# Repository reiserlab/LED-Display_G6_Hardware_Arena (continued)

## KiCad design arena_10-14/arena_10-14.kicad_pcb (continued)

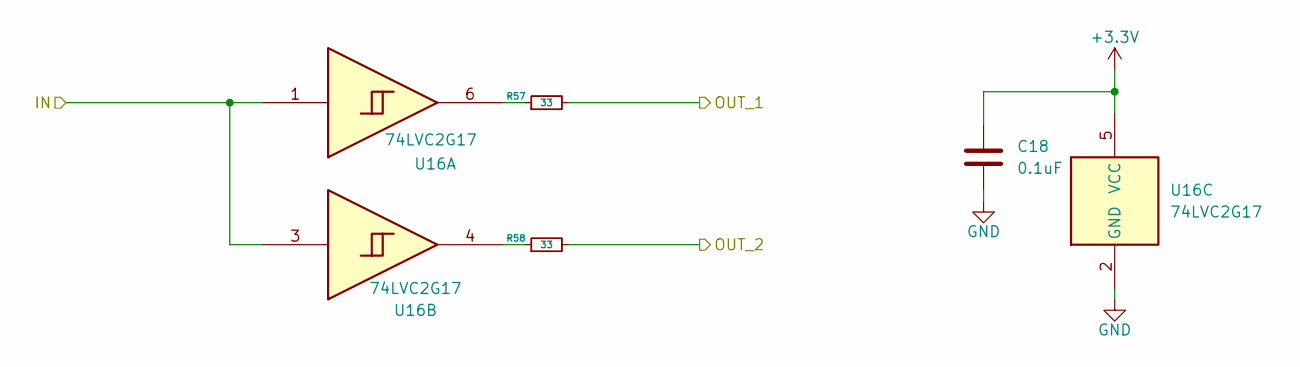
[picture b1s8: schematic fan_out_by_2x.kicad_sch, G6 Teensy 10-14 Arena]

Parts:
C18: 0.1uF; C_0402_1005Metric; LCSC Part # C1525
R57, R58: 33; R_0402_1005Metric; LCSC Part # C25105
U16: 74LVC2G17; SOT-23-6; LCSC Part # C7394037

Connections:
+3.3V: C18.1, U16.5 (VCC); also elsewhere on the board
/Fan Out/PAN.CS_00_P1: R58.2; also elsewhere on the board
/Fan Out/PAN.CS_00_P6: R57.2; also elsewhere on the board
/Fan Out/TNY.CS_00: U16.1, U16.3; also elsewhere on the board
GND: C18.2, U16.2 (GND); also elsewhere on the board
unnamed: R57.1, U16.6
unnamed: R58.1, U16.4

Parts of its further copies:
C19, C20, C21, C22, C23, C24, C25, C26, C27, C28, C29, C30, C31, C32, C33, C34, C35, C36, C37: 0.1uF; C_0402_1005Metric; LCSC Part # C1525
R59, R60, R61, R62, R63, R64, R65, R66, R67, R68, R69, R70, R71, R72, R73, R74, R75, R76, R77, R78, R79, R80, R81, R82, R83, R84, R85, R86, R87, R88, R89, R90, R91, R92, R93, R94, R95, R96: 33; R_0402_1005Metric; LCSC Part # C25105
U17, U18, U19, U20, U21, U22, U23, U24, U25, U26, U27, U28, U29, U30, U31, U32, U33, U34, U35: 74LVC2G17; SOT-23-6; LCSC Part # C7394037

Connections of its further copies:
+3.3V: C19.1, C20.1, C21.1, C22.1, C23.1, C24.1, C25.1, C26.1, C27.1, C28.1, C29.1, C30.1, C31.1, C32.1, C33.1, C34.1, C35.1, C36.1, C37.1, U17.5 (VCC), U18.5 (VCC), U19.5 (VCC), U20.5 (VCC), U21.5 (VCC), U22.5 (VCC), U23.5 (VCC), U24.5 (VCC), U25.5 (VCC), U26.5 (VCC), U27.5 (VCC), U28.5 (VCC), U29.5 (VCC), U30.5 (VCC), U31.5 (VCC), U32.5 (VCC), U33.5 (VCC), U34.5 (VCC), U35.5 (VCC); also elsewhere on the board
/Fan Out/PAN.CS_01_P1: R60.2; also elsewhere on the board
/Fan Out/PAN.CS_01_P6: R59.2; also elsewhere on the board
/Fan Out/PAN.CS_02_P1: R62.2; also elsewhere on the board
/Fan Out/PAN.CS_02_P6: R61.2; also elsewhere on the board
/Fan Out/PAN.CS_03_P1: R64.2; also elsewhere on the board
/Fan Out/PAN.CS_03_P6: R63.2; also elsewhere on the board
/Fan Out/PAN.CS_04_P2: R66.2; also elsewhere on the board
/Fan Out/PAN.CS_04_P7: R65.2; also elsewhere on the board
/Fan Out/PAN.CS_05_P2: R68.2; also elsewhere on the board
/Fan Out/PAN.CS_05_P7: R67.2; also elsewhere on the board
/Fan Out/PAN.CS_06_P2: R70.2; also elsewhere on the board
/Fan Out/PAN.CS_06_P7: R69.2; also elsewhere on the board
/Fan Out/PAN.CS_07_P2: R72.2; also elsewhere on the board
/Fan Out/PAN.CS_07_P7: R71.2; also elsewhere on the board
/Fan Out/PAN.CS_08_P3: R74.2; also elsewhere on the board
/Fan Out/PAN.CS_08_P8: R73.2; also elsewhere on the board
/Fan Out/PAN.CS_09_P3: R76.2; also elsewhere on the board
/Fan Out/PAN.CS_09_P8: R75.2; also elsewhere on the board
/Fan Out/PAN.CS_10_P3: R78.2; also elsewhere on the board
/Fan Out/PAN.CS_10_P8: R77.2; also elsewhere on the board
/Fan Out/PAN.CS_11_P3: R80.2; also elsewhere on the board
/Fan Out/PAN.CS_11_P8: R79.2; also elsewhere on the board
/Fan Out/PAN.CS_12_P4: R82.2; also elsewhere on the board
/Fan Out/PAN.CS_12_P9: R81.2; also elsewhere on the board
/Fan Out/PAN.CS_13_P4: R84.2; also elsewhere on the board
/Fan Out/PAN.CS_13_P9: R83.2; also elsewhere on the board
/Fan Out/PAN.CS_14_P4: R86.2; also elsewhere on the board
/Fan Out/PAN.CS_14_P9: R85.2; also elsewhere on the board
/Fan Out/PAN.CS_15_P4: R88.2; also elsewhere on the board
/Fan Out/PAN.CS_15_P9: R87.2; also elsewhere on the board
/Fan Out/PAN.CS_16_P5: R90.2; also elsewhere on the board
/Fan Out/PAN.CS_16_P10: R89.2; also elsewhere on the board
/Fan Out/PAN.CS_17_P5: R92.2; also elsewhere on the board
/Fan Out/PAN.CS_17_P10: R91.2; also elsewhere on the board
/Fan Out/PAN.CS_18_P5: R94.2; also elsewhere on the board
/Fan Out/PAN.CS_18_P10: R93.2; also elsewhere on the board
/Fan Out/PAN.CS_19_P5: R96.2; also elsewhere on the board
/Fan Out/PAN.CS_19_P10: R95.2; also elsewhere on the board
/Fan Out/TNY.CS_01: U17.1, U17.3; also elsewhere on the board
/Fan Out/TNY.CS_02: U18.1, U18.3; also elsewhere on the board
/Fan Out/TNY.CS_03: U19.1, U19.3; also elsewhere on the board
/Fan Out/TNY.CS_04: U20.1, U20.3; also elsewhere on the board
/Fan Out/TNY.CS_05: U21.1, U21.3; also elsewhere on the board
/Fan Out/TNY.CS_06: U22.1, U22.3; also elsewhere on the board
/Fan Out/TNY.CS_07: U23.1, U23.3; also elsewhere on the board
/Fan Out/TNY.CS_08: U24.1, U24.3; also elsewhere on the board
/Fan Out/TNY.CS_09: U25.1, U25.3; also elsewhere on the board
/Fan Out/TNY.CS_10: U26.1, U26.3; also elsewhere on the board
/Fan Out/TNY.CS_11: U27.1, U27.3; also elsewhere on the board
/Fan Out/TNY.CS_12: U28.1, U28.3; also elsewhere on the board
/Fan Out/TNY.CS_13: U29.1, U29.3; also elsewhere on the board
/Fan Out/TNY.CS_14: U30.1, U30.3; also elsewhere on the board
/Fan Out/TNY.CS_15: U31.1, U31.3; also elsewhere on the board
/Fan Out/TNY.CS_16: U32.1, U32.3; also elsewhere on the board
/Fan Out/TNY.CS_17: U33.1, U33.3; also elsewhere on the board
/Fan Out/TNY.CS_18: U34.1, U34.3; also elsewhere on the board
/Fan Out/TNY.CS_19: U35.1, U35.3; also elsewhere on the board
GND: C19.2, C20.2, C21.2, C22.2, C23.2, C24.2, C25.2, C26.2, C27.2, C28.2, C29.2, C30.2, C31.2, C32.2, C33.2, C34.2, C35.2, C36.2, C37.2, U17.2 (GND), U18.2 (GND), U19.2 (GND), U20.2 (GND), U21.2 (GND), U22.2 (GND), U23.2 (GND), U24.2 (GND), U25.2 (GND), U26.2 (GND), U27.2 (GND), U28.2 (GND), U29.2 (GND), U30.2 (GND), U31.2 (GND), U32.2 (GND), U33.2 (GND), U34.2 (GND), U35.2 (GND); also elsewhere on the board
unnamed: R59.1, U17.6
unnamed: R60.1, U17.4
unnamed: R61.1, U18.6
unnamed: R62.1, U18.4
unnamed: R63.1, U19.6
unnamed: R64.1, U19.4
unnamed: R65.1, U20.6
unnamed: R66.1, U20.4
unnamed: R67.1, U21.6
unnamed: R68.1, U21.4
unnamed: R69.1, U22.6
unnamed: R70.1, U22.4
unnamed: R71.1, U23.6
unnamed: R72.1, U23.4
unnamed: R73.1, U24.6
unnamed: R74.1, U24.4
unnamed: R75.1, U25.6
unnamed: R76.1, U25.4
unnamed: R77.1, U26.6
unnamed: R78.1, U26.4
unnamed: R79.1, U27.6
unnamed: R80.1, U27.4
unnamed: R81.1, U28.6
unnamed: R82.1, U28.4
unnamed: R83.1, U29.6
unnamed: R84.1, U29.4
unnamed: R85.1, U30.6
unnamed: R86.1, U30.4
unnamed: R87.1, U31.6
unnamed: R88.1, U31.4
unnamed: R89.1, U32.6
unnamed: R90.1, U32.4
unnamed: R91.1, U33.6
unnamed: R92.1, U33.4
unnamed: R93.1, U34.6
unnamed: R94.1, U34.4
unnamed: R95.1, U35.6
unnamed: R96.1, U35.4

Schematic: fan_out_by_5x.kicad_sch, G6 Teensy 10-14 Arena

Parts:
C6, C7, C8: 0.1uF; C_0402_1005Metric; LCSC Part # C1525
R33, R34, R35, R36, R37, R38: 33; R_0402_1005Metric; LCSC Part # C25105
U4, U5, U6: 74LVC2G17; SOT-23-6; LCSC Part # C7394037

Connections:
+3.3V: C6.1, C7.1, C8.1, U4.5 (VCC), U5.5 (VCC), U6.5 (VCC); also elsewhere on the board
/Fan Out/PAN.SCK_B0_P1: R33.2; also elsewhere on the board
/Fan Out/PAN.SCK_B0_P2: R34.2; also elsewhere on the board
/Fan Out/PAN.SCK_B0_P3: R35.2; also elsewhere on the board
/Fan Out/PAN.SCK_B0_P4: R36.2; also elsewhere on the board
/Fan Out/PAN.SCK_B0_P5: R37.2; also elsewhere on the board
/Fan Out/SCK B0 fan out to P1-P6/OUT_6: R38.2
/Fan Out/TNY.SCK_B0: U4.1, U4.3, U5.1, U5.3, U6.1, U6.3; also elsewhere on the board
GND: C6.2, C7.2, C8.2, U4.2 (GND), U5.2 (GND), U6.2 (GND); also elsewhere on the board
unnamed: R33.1, U4.6
unnamed: R34.1, U4.4
unnamed: R35.1, U5.6
unnamed: R36.1, U5.4
unnamed: R37.1, U6.6
unnamed: R38.1, U6.4

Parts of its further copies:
C9, C10, C11, C12, C13, C14, C15, C16, C17, C38, C39, C40, C41, C42, C43: 0.1uF; C_0402_1005Metric; LCSC Part # C1525
R39, R40, R41, R42, R43, R44, R45, R46, R47, R48, R49, R50, R51, R52, R53, R54, R55, R56, R97, R98, R99, R100, R101, R102, R103, R104, R105, R106, R107, R108: 33; R_0402_1005Metric; LCSC Part # C25105
U7, U8, U9, U10, U11, U12, U13, U14, U15, U36, U37, U38, U39, U40, U41: 74LVC2G17; SOT-23-6; LCSC Part # C7394037

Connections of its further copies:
+3.3V: C9.1, C10.1, C11.1, C12.1, C13.1, C14.1, C15.1, C16.1, C17.1, C38.1, C39.1, C40.1, C41.1, C42.1, C43.1, U7.5 (VCC), U8.5 (VCC), U9.5 (VCC), U10.5 (VCC), U11.5 (VCC), U12.5 (VCC), U13.5 (VCC), U14.5 (VCC), U15.5 (VCC), U36.5 (VCC), U37.5 (VCC), U38.5 (VCC), U39.5 (VCC), U40.5 (VCC), U41.5 (VCC); also elsewhere on the board
/Fan Out/COPI B0 fan out to P1-P6/OUT_6: R44.2
/Fan Out/COPI B1 fan out to P6-P10/OUT_6: R56.2
/Fan Out/EINT fan out to P1-P5/OUT_6: R108.2
/Fan Out/EINT fan out to P6-P10/OUT_6: R102.2
/Fan Out/PAN.COPI_B0_P1: R39.2; also elsewhere on the board
/Fan Out/PAN.COPI_B0_P2: R40.2; also elsewhere on the board
/Fan Out/PAN.COPI_B0_P3: R41.2; also elsewhere on the board
/Fan Out/PAN.COPI_B0_P4: R42.2; also elsewhere on the board
/Fan Out/PAN.COPI_B0_P5: R43.2; also elsewhere on the board
/Fan Out/PAN.COPI_B1_P6: R51.2; also elsewhere on the board
/Fan Out/PAN.COPI_B1_P7: R52.2; also elsewhere on the board
/Fan Out/PAN.COPI_B1_P8: R53.2; also elsewhere on the board
/Fan Out/PAN.COPI_B1_P9: R54.2; also elsewhere on the board
/Fan Out/PAN.COPI_B1_P10: R55.2; also elsewhere on the board
/Fan Out/PAN.EINT_P1: R103.2; also elsewhere on the board
/Fan Out/PAN.EINT_P2: R104.2; also elsewhere on the board
/Fan Out/PAN.EINT_P3: R105.2; also elsewhere on the board
/Fan Out/PAN.EINT_P4: R106.2; also elsewhere on the board
/Fan Out/PAN.EINT_P5: R107.2; also elsewhere on the board
/Fan Out/PAN.EINT_P6: R97.2; also elsewhere on the board
/Fan Out/PAN.EINT_P7: R98.2; also elsewhere on the board
/Fan Out/PAN.EINT_P8: R99.2; also elsewhere on the board
/Fan Out/PAN.EINT_P9: R100.2; also elsewhere on the board
/Fan Out/PAN.EINT_P10: R101.2; also elsewhere on the board
/Fan Out/PAN.SCK_B1_P6: R45.2; also elsewhere on the board
/Fan Out/PAN.SCK_B1_P7: R46.2; also elsewhere on the board
/Fan Out/PAN.SCK_B1_P8: R47.2; also elsewhere on the board
/Fan Out/PAN.SCK_B1_P9: R48.2; also elsewhere on the board
/Fan Out/PAN.SCK_B1_P10: R49.2; also elsewhere on the board
/Fan Out/SCK B1 fan out to P6-P10/OUT_6: R50.2
/Fan Out/TNY.COPI_B0: U7.1, U7.3, U8.1, U8.3, U9.1, U9.3; also elsewhere on the board
/Fan Out/TNY.COPI_B1: U13.1, U13.3, U14.1, U14.3, U15.1, U15.3; also elsewhere on the board
/Fan Out/TNY.EINT: U36.1, U36.3, U37.1, U37.3, U38.1, U38.3, U39.1, U39.3, U40.1, U40.3, U41.1, U41.3; also elsewhere on the board
/Fan Out/TNY.SCK_B1: U10.1, U10.3, U11.1, U11.3, U12.1, U12.3; also elsewhere on the board
GND: C9.2, C10.2, C11.2, C12.2, C13.2, C14.2, C15.2, C16.2, C17.2, C38.2, C39.2, C40.2, C41.2, C42.2, C43.2, U7.2 (GND), U8.2 (GND), U9.2 (GND), U10.2 (GND), U11.2 (GND), U12.2 (GND), U13.2 (GND), U14.2 (GND), U15.2 (GND), U36.2 (GND), U37.2 (GND), U38.2 (GND), U39.2 (GND), U40.2 (GND), U41.2 (GND); also elsewhere on the board
unnamed: R39.1, U7.6
unnamed: R40.1, U7.4
unnamed: R41.1, U8.6
unnamed: R42.1, U8.4
unnamed: R43.1, U9.6
unnamed: R44.1, U9.4
unnamed: R45.1, U10.6
unnamed: R46.1, U10.4
unnamed: R47.1, U11.6
unnamed: R48.1, U11.4
unnamed: R49.1, U12.6
unnamed: R50.1, U12.4
unnamed: R51.1, U13.6
unnamed: R52.1, U13.4
unnamed: R53.1, U14.6
unnamed: R54.1, U14.4
unnamed: R55.1, U15.6
unnamed: R56.1, U15.4
unnamed: R97.1, U36.6
unnamed: R98.1, U36.4
unnamed: R99.1, U37.6
unnamed: R100.1, U37.4
unnamed: R101.1, U38.6
unnamed: R102.1, U38.4
unnamed: R103.1, U39.6
unnamed: R104.1, U39.4
unnamed: R105.1, U40.6
unnamed: R106.1, U40.4
unnamed: R107.1, U41.6
unnamed: R108.1, U41.4

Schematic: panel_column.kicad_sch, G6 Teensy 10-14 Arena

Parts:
C48: 100uF; C_1210_3225Metric; LCSC Part # C7432790
F1: 1.1A PTC; Fuse_1206_3216Metric; LCSC Part # C126818
J7, J8: Conn_01x05; PinSocket_1x05_P2.54mm_Vertical; LCSC Part # C50950
P1: NA; Panel_Silk; not fitted

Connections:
+5V: F1.1; also elsewhere on the board
/Panels/Panel Column P1/Column Buffer/CIPO_IN: J7.5; also elsewhere on the board
/Panels/Panel Column P1/Column Buffer/COPI_OUT: J7.4; also elsewhere on the board
/Panels/Panel Column P1/Column Buffer/CS0_OUT: J8.1; also elsewhere on the board
/Panels/Panel Column P1/Column Buffer/CS1_OUT: J8.2; also elsewhere on the board
/Panels/Panel Column P1/Column Buffer/CS2_OUT: J8.3; also elsewhere on the board
/Panels/Panel Column P1/Column Buffer/CS_3OUT: J8.4; also elsewhere on the board
/Panels/Panel Column P1/Column Buffer/EINT_OUT: J8.5; also elsewhere on the board
/Panels/Panel Column P1/Column Buffer/SCK_OUT: J7.3; also elsewhere on the board
GND: C48.1, J7.2; also elsewhere on the board
unnamed: C48.2, F1.2, J7.1

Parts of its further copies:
C49, C54, C59, C64, C69, C74, C79, C84, C152: 100uF; C_1210_3225Metric; LCSC Part # C7432790
F2, F3, F4, F5, F6, F7, F8, F9, F10: 1.1A PTC; Fuse_1206_3216Metric; LCSC Part # C126818
J9, J10, J11, J12, J13, J14, J15, J16, J17, J18, J19, J20, J21, J22, J23, J24, J32, J33: Conn_01x05; PinSocket_1x05_P2.54mm_Vertical; LCSC Part # C50950
P2, P3, P4, P5, P6, P7, P8, P9, P10: NA; Panel_Silk; not fitted

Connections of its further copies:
+5V: F2.1, F3.1, F4.1, F5.1, F6.1, F7.1, F8.1, F9.1, F10.1; also elsewhere on the board
/Panels/Panel Column P2/Column Buffer/CIPO_IN: J9.5; also elsewhere on the board
/Panels/Panel Column P2/Column Buffer/COPI_OUT: J9.4; also elsewhere on the board
/Panels/Panel Column P2/Column Buffer/CS0_OUT: J10.1; also elsewhere on the board
/Panels/Panel Column P2/Column Buffer/CS1_OUT: J10.2; also elsewhere on the board
/Panels/Panel Column P2/Column Buffer/CS2_OUT: J10.3; also elsewhere on the board
/Panels/Panel Column P2/Column Buffer/CS_3OUT: J10.4; also elsewhere on the board
/Panels/Panel Column P2/Column Buffer/EINT_OUT: J10.5; also elsewhere on the board
/Panels/Panel Column P2/Column Buffer/SCK_OUT: J9.3; also elsewhere on the board
/Panels/Panel Column P3/Column Buffer/CIPO_IN: J11.5; also elsewhere on the board
/Panels/Panel Column P3/Column Buffer/COPI_OUT: J11.4; also elsewhere on the board
/Panels/Panel Column P3/Column Buffer/CS0_OUT: J12.1; also elsewhere on the board
/Panels/Panel Column P3/Column Buffer/CS1_OUT: J12.2; also elsewhere on the board
/Panels/Panel Column P3/Column Buffer/CS2_OUT: J12.3; also elsewhere on the board
/Panels/Panel Column P3/Column Buffer/CS_3OUT: J12.4; also elsewhere on the board
/Panels/Panel Column P3/Column Buffer/EINT_OUT: J12.5; also elsewhere on the board
/Panels/Panel Column P3/Column Buffer/SCK_OUT: J11.3; also elsewhere on the board
/Panels/Panel Column P4/Column Buffer/CIPO_IN: J13.5; also elsewhere on the board
/Panels/Panel Column P4/Column Buffer/COPI_OUT: J13.4; also elsewhere on the board
/Panels/Panel Column P4/Column Buffer/CS0_OUT: J14.1; also elsewhere on the board
/Panels/Panel Column P4/Column Buffer/CS1_OUT: J14.2; also elsewhere on the board
/Panels/Panel Column P4/Column Buffer/CS2_OUT: J14.3; also elsewhere on the board
/Panels/Panel Column P4/Column Buffer/CS_3OUT: J14.4; also elsewhere on the board
/Panels/Panel Column P4/Column Buffer/EINT_OUT: J14.5; also elsewhere on the board
/Panels/Panel Column P4/Column Buffer/SCK_OUT: J13.3; also elsewhere on the board
/Panels/Panel Column P5/Column Buffer/CIPO_IN: J15.5; also elsewhere on the board
/Panels/Panel Column P5/Column Buffer/COPI_OUT: J15.4; also elsewhere on the board
/Panels/Panel Column P5/Column Buffer/CS0_OUT: J16.1; also elsewhere on the board
/Panels/Panel Column P5/Column Buffer/CS1_OUT: J16.2; also elsewhere on the board
/Panels/Panel Column P5/Column Buffer/CS2_OUT: J16.3; also elsewhere on the board
/Panels/Panel Column P5/Column Buffer/CS_3OUT: J16.4; also elsewhere on the board
/Panels/Panel Column P5/Column Buffer/EINT_OUT: J16.5; also elsewhere on the board
/Panels/Panel Column P5/Column Buffer/SCK_OUT: J15.3; also elsewhere on the board
/Panels/Panel Column P6/Column Buffer/CIPO_IN: J32.5; also elsewhere on the board
/Panels/Panel Column P6/Column Buffer/COPI_OUT: J32.4; also elsewhere on the board
/Panels/Panel Column P6/Column Buffer/CS0_OUT: J33.1; also elsewhere on the board
/Panels/Panel Column P6/Column Buffer/CS1_OUT: J33.2; also elsewhere on the board
/Panels/Panel Column P6/Column Buffer/CS2_OUT: J33.3; also elsewhere on the board
/Panels/Panel Column P6/Column Buffer/CS_3OUT: J33.4; also elsewhere on the board
/Panels/Panel Column P6/Column Buffer/EINT_OUT: J33.5; also elsewhere on the board
/Panels/Panel Column P6/Column Buffer/SCK_OUT: J32.3; also elsewhere on the board
/Panels/Panel Column P7/Column Buffer/CIPO_IN: J17.5; also elsewhere on the board
/Panels/Panel Column P7/Column Buffer/COPI_OUT: J17.4; also elsewhere on the board
/Panels/Panel Column P7/Column Buffer/CS0_OUT: J18.1; also elsewhere on the board
/Panels/Panel Column P7/Column Buffer/CS1_OUT: J18.2; also elsewhere on the board
/Panels/Panel Column P7/Column Buffer/CS2_OUT: J18.3; also elsewhere on the board
/Panels/Panel Column P7/Column Buffer/CS_3OUT: J18.4; also elsewhere on the board
/Panels/Panel Column P7/Column Buffer/EINT_OUT: J18.5; also elsewhere on the board
/Panels/Panel Column P7/Column Buffer/SCK_OUT: J17.3; also elsewhere on the board
/Panels/Panel Column P8/Column Buffer/CIPO_IN: J19.5; also elsewhere on the board
/Panels/Panel Column P8/Column Buffer/COPI_OUT: J19.4; also elsewhere on the board
/Panels/Panel Column P8/Column Buffer/CS0_OUT: J20.1; also elsewhere on the board
/Panels/Panel Column P8/Column Buffer/CS1_OUT: J20.2; also elsewhere on the board
/Panels/Panel Column P8/Column Buffer/CS2_OUT: J20.3; also elsewhere on the board
/Panels/Panel Column P8/Column Buffer/CS_3OUT: J20.4; also elsewhere on the board
/Panels/Panel Column P8/Column Buffer/EINT_OUT: J20.5; also elsewhere on the board
/Panels/Panel Column P8/Column Buffer/SCK_OUT: J19.3; also elsewhere on the board
/Panels/Panel Column P9/Column Buffer/CIPO_IN: J21.5; also elsewhere on the board
/Panels/Panel Column P9/Column Buffer/COPI_OUT: J21.4; also elsewhere on the board
/Panels/Panel Column P9/Column Buffer/CS0_OUT: J22.1; also elsewhere on the board
/Panels/Panel Column P9/Column Buffer/CS1_OUT: J22.2; also elsewhere on the board
/Panels/Panel Column P9/Column Buffer/CS2_OUT: J22.3; also elsewhere on the board
/Panels/Panel Column P9/Column Buffer/CS_3OUT: J22.4; also elsewhere on the board
/Panels/Panel Column P9/Column Buffer/EINT_OUT: J22.5; also elsewhere on the board
/Panels/Panel Column P9/Column Buffer/SCK_OUT: J21.3; also elsewhere on the board
/Panels/Panel Column P10/Column Buffer/CIPO_IN: J23.5; also elsewhere on the board
/Panels/Panel Column P10/Column Buffer/COPI_OUT: J23.4; also elsewhere on the board
/Panels/Panel Column P10/Column Buffer/CS0_OUT: J24.1; also elsewhere on the board
/Panels/Panel Column P10/Column Buffer/CS1_OUT: J24.2; also elsewhere on the board
/Panels/Panel Column P10/Column Buffer/CS2_OUT: J24.3; also elsewhere on the board
/Panels/Panel Column P10/Column Buffer/CS_3OUT: J24.4; also elsewhere on the board
/Panels/Panel Column P10/Column Buffer/EINT_OUT: J24.5; also elsewhere on the board
/Panels/Panel Column P10/Column Buffer/SCK_OUT: J23.3; also elsewhere on the board
GND: C49.1, C54.1, C59.1, C64.1, C69.1, C74.1, C79.1, C84.1, C152.1, J9.2, J11.2, J13.2, J15.2, J17.2, J19.2, J21.2, J23.2, J32.2; also elsewhere on the board
unnamed: C49.2, F2.2, J9.1
unnamed: C54.2, F3.2, J11.1
unnamed: C59.2, F4.2, J13.1
unnamed: C64.2, F5.2, J15.1
unnamed: C69.2, F7.2, J17.1
unnamed: C74.2, F8.2, J19.1
unnamed: C79.2, F9.2, J21.1
unnamed: C84.2, F10.2, J23.1
unnamed: C152.2, F6.2, J32.1

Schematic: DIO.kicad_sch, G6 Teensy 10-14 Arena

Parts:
C89, C90: 0.1uF; C_0402_1005Metric; LCSC Part # C1525
J6: Conn_Coaxial; BNC_HenryTech_HL-BNC_KHDA; LCSC Part # C19712152
U3: SN74LVC1T45DBV; SOT-23-6; LCSC Part # C7843

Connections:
+3.3V: C90.1, U3.1 (VCCA); also elsewhere on the board
+5V: C89.1, U3.6 (VCCB); also elsewhere on the board
/Teensy/D35_0_3V3: U3.3 (A); also elsewhere on the board
/Teensy/DIO2/DIR: U3.5 (DIR); also elsewhere on the board
GND: C89.2, C90.2, J6.2 (Ext), U3.2 (GND); also elsewhere on the board
unnamed: J6.1 (In), U3.4 (B)

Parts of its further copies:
C91, C92, C93, C139, C140, C141: 0.1uF; C_0402_1005Metric; LCSC Part # C1525
J25, J26, J34: Conn_Coaxial; BNC_HenryTech_HL-BNC_KHDA; LCSC Part # C19712152
U78, U79, U80: SN74LVC1T45DBV; SOT-23-6; LCSC Part # C7843

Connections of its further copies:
+3.3V: C92.1, C139.1, C141.1, U78.1 (VCCA), U79.1 (VCCA), U80.1 (VCCA); also elsewhere on the board
+5V: C91.1, C93.1, C140.1, U78.6 (VCCB), U79.6 (VCCB), U80.6 (VCCB); also elsewhere on the board
/Teensy/D29_0_3V3: U78.3 (A); also elsewhere on the board
/Teensy/DIO1/DIR: U78.5 (DIR); also elsewhere on the board
/Teensy/DIO3/A: U80.3 (A); also elsewhere on the board
/Teensy/DIO3/DIR: U79.5 (DIR), U80.5 (DIR); also elsewhere on the board
/Teensy/DIO4/A: U79.3 (A); also elsewhere on the board
GND: C91.2, C92.2, C93.2, C139.2, C140.2, C141.2, J25.2 (Ext), J26.2 (Ext), J34.2 (Ext), U78.2 (GND), U79.2 (GND), U80.2 (GND); also elsewhere on the board
unnamed: J25.1 (In), U78.4 (B)
unnamed: J26.1 (In), U79.4 (B)
unnamed: J34.1 (In), U80.4 (B)
